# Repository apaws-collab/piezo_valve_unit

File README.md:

# piezo_valve_unit
## Data-driven pressure control based on Gaussian processes

Welcome to this project that demonstrates a data-driven pressure controller for Festo’s VEAE piezoelectric valves.

**Disclaimer**: This code is not plug-and-play due to variability in hardware and control system setups. However, it serves as a comprehensive guideline for building a high-accuracy pressure controller, following the outlined implementation steps.

---

### CAD  
The block and the cap are created in FreeCAD V1.0
_work in progress_:
- [x] Valve block (main part), SLA printed
- [x] Cap, FDM printed
- [ ] Assembly and parts list
- [ ] Construction details

### Electric circuit
The distributor board is created in KiCAD V8.0
_work in progress_:
- [x] Overview
- [x] Layout
- [x] Circuit, KiCad 9.0
- [ ] BOM

### m-code  
This MATLAB code provides a reference implementation of a pressure control framework for soft pneumatic actuators (SPAs), using Festo's VEAE piezo valves. Two valves are assembled in an SLA-printed housing to form a compact 3/3 valve unit. Due to its small size, the valve unit is designed to be mounted directly on or near the actuator. This proximity, combined with volume-adaptive control, enables high-precision pressure regulation.

The code was developed and tested on a MATLAB real-time target machine but is structured to be easily ported to microcontrollers, as it relies on LUT (lookup table) based implementations of the Gaussian processes.

The only external dependency is Peter Corke’s Robotics Toolbox for MATLAB, which is used for motion generation (see <https://petercorke.com/toolboxes/robotics-toolbox/>).

**Procedure:**  
Start with the `pressure_control` script. It will guide you through the complete implementation process.

---

### License

This program is free software: you can redistribute it and/or modify
it under the terms of the GNU General Public License as published by
the Free Software Foundation, either version 3 of the License, or
(at your option) any later version.

This program is distributed in the hope that it will be useful,
but WITHOUT ANY WARRANTY; without even the implied warranty of
MERCHANTABILITY or FITNESS FOR A PARTICULAR PURPOSE.  See the
GNU General Public License for more details.

You should have received a copy of the GNU General Public License
along with this program.  If not, see <http://www.gnu.org/licenses/>

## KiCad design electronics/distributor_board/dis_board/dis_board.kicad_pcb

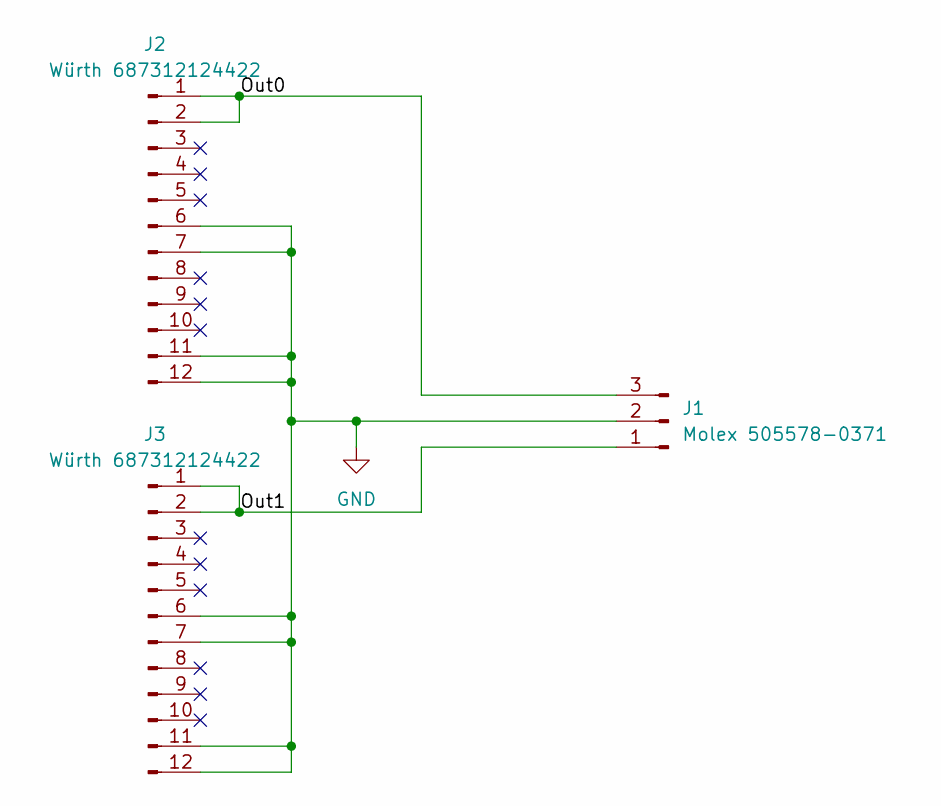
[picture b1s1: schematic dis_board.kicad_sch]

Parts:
J1: Molex 505578-0371; 505578-0371
J2, J3: Würth 687312124422; 687312124422

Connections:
/Out0: J1.3, J2.1, J2.2
/Out1: J1.1, J3.1, J3.2
GND: J1.2, J2.6, J2.7, J2.11, J2.12, J3.6, J3.7, J3.11, J3.12

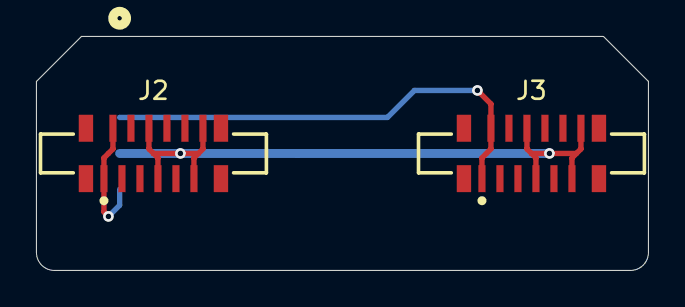
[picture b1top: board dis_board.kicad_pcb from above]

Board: 2 copper layers, 34.0 x 13.0 mm, 3 parts (1 on the bottom side), 3 nets.

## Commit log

2025-08-05 pressure controller code added
2025-08-20 Electronics folder added
2025-08-20 move readme
2025-08-20 placeholder for CAD data
2025-08-27 CAD valve block added
    designed in FreeCAD V 1.0
2025-08-27 Update README.md
    updated WIP
2025-09-03 CAD valve cap added
2025-11-28 circuit for the distributor board added
    this boards connects both piezo valves to the driver board. KiCad 9.0
2025-11-28 Revise project status in README.md
    Updated the progress status of CAD and electric circuit components in the README.
